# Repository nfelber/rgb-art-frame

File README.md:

# RGB Art Frame

DIY art stand for small engraved artworks based on a custom pcb with several RGB effects.

## The PCB

This design is based on a custom printed circuit board made with KiCad for which all the project files are found in this repository.
The file `design-files/prism-fx_v1_1_gerber.zip` can be uploaded directly to most manufacturers' websites to order your own. You will find the list of all required components for hand soldering in `./design-files/pcb-components-list.csv`.

## The base

The base is laser cut using wood and acrylic (with the intermediate part alternatively 3D printed in translucent material) and held together with four 16mm M2.5 screws.
I also designed a simple cap for the knob which you can 3D print.
Everything was designed using FreeCAD in the project file `model.FCStd`.
You will also find `.stl` and `.dxf` files in the `design-files/` to use straightaway.

Note that some metrics may need to be slightly adjusted depending on the laser cutter or 3D printer.

## The arts

Pretty much anything can be used with the RGB base, but I personnally decided to engrave AI-generated images on wood with an etched layer of acryllic on top to capture light and highlight the edges of the pictures.
I'm not sharing the arts here, as the point to me is that they are unique and personnal.
Be creative!

## The program

The ATtiny85 microcontroller can be easily programmed using an Arduino board as a programmer and with the help of the Arduino IDE.
Many tutorials are available online.
Please note that the USB-C port is only used for powering the circuit board, thus it is **not** possible to program the microcontroller throught it.
Use the PCB's 6 header pins instead.
In order to work with the default `ArduinoISP` sketch, connect them to the Arduino GPIOs as shown below:

```console
      The 6 pins
 .   .   .   .   .   .
[ ] [ ] [ ] [ ] [ ] [ ]
 |   |   |   |   |   |  
 |   |   |   |   |   |    

 +   -   10  13  12  11  <- Arduino GPIOs
```

You will find an example sketch in `prism_fx/prism_fx.ino`.
The sketch shows a way of using interrupts to react to knobs events, the `Adafruit_NeoPixel` library to control the RGB Neopixels, and to storing the last effect state in the permanent EEPROM storage.
Feel free to customize it with you own effects.

In the example sketch, the device cycles through the 3 following modes by pressing down the knob:

1. Effect mode: turing the knob changes the lighting effect among the following:
	- Spectrum: slowly cycle through every color hues.
	- Rainbow: like spectrum, but the LEDs are not synchronized.
	- Static: static color.
	- Fire: fire/candle effect of a static color.
	- Flash: flashes randomly in white.
	- Test: display the current parameter value in binary.
2. Parameter mode: turing the knob changes the value of a parameter between 0 and 31, which has the following result depending on the effect:
	- Spectrum: change cycle speed.
	- Rainbow: change randbow spread in the hue space.
	- Static: change the color.
	- Fire: change the color.
	- Flash: change the frequency of the flashes.
	- Test: display the current parameter value in binary.
3. Brightness mode: turning the knob changes the brightness of the LEDs.

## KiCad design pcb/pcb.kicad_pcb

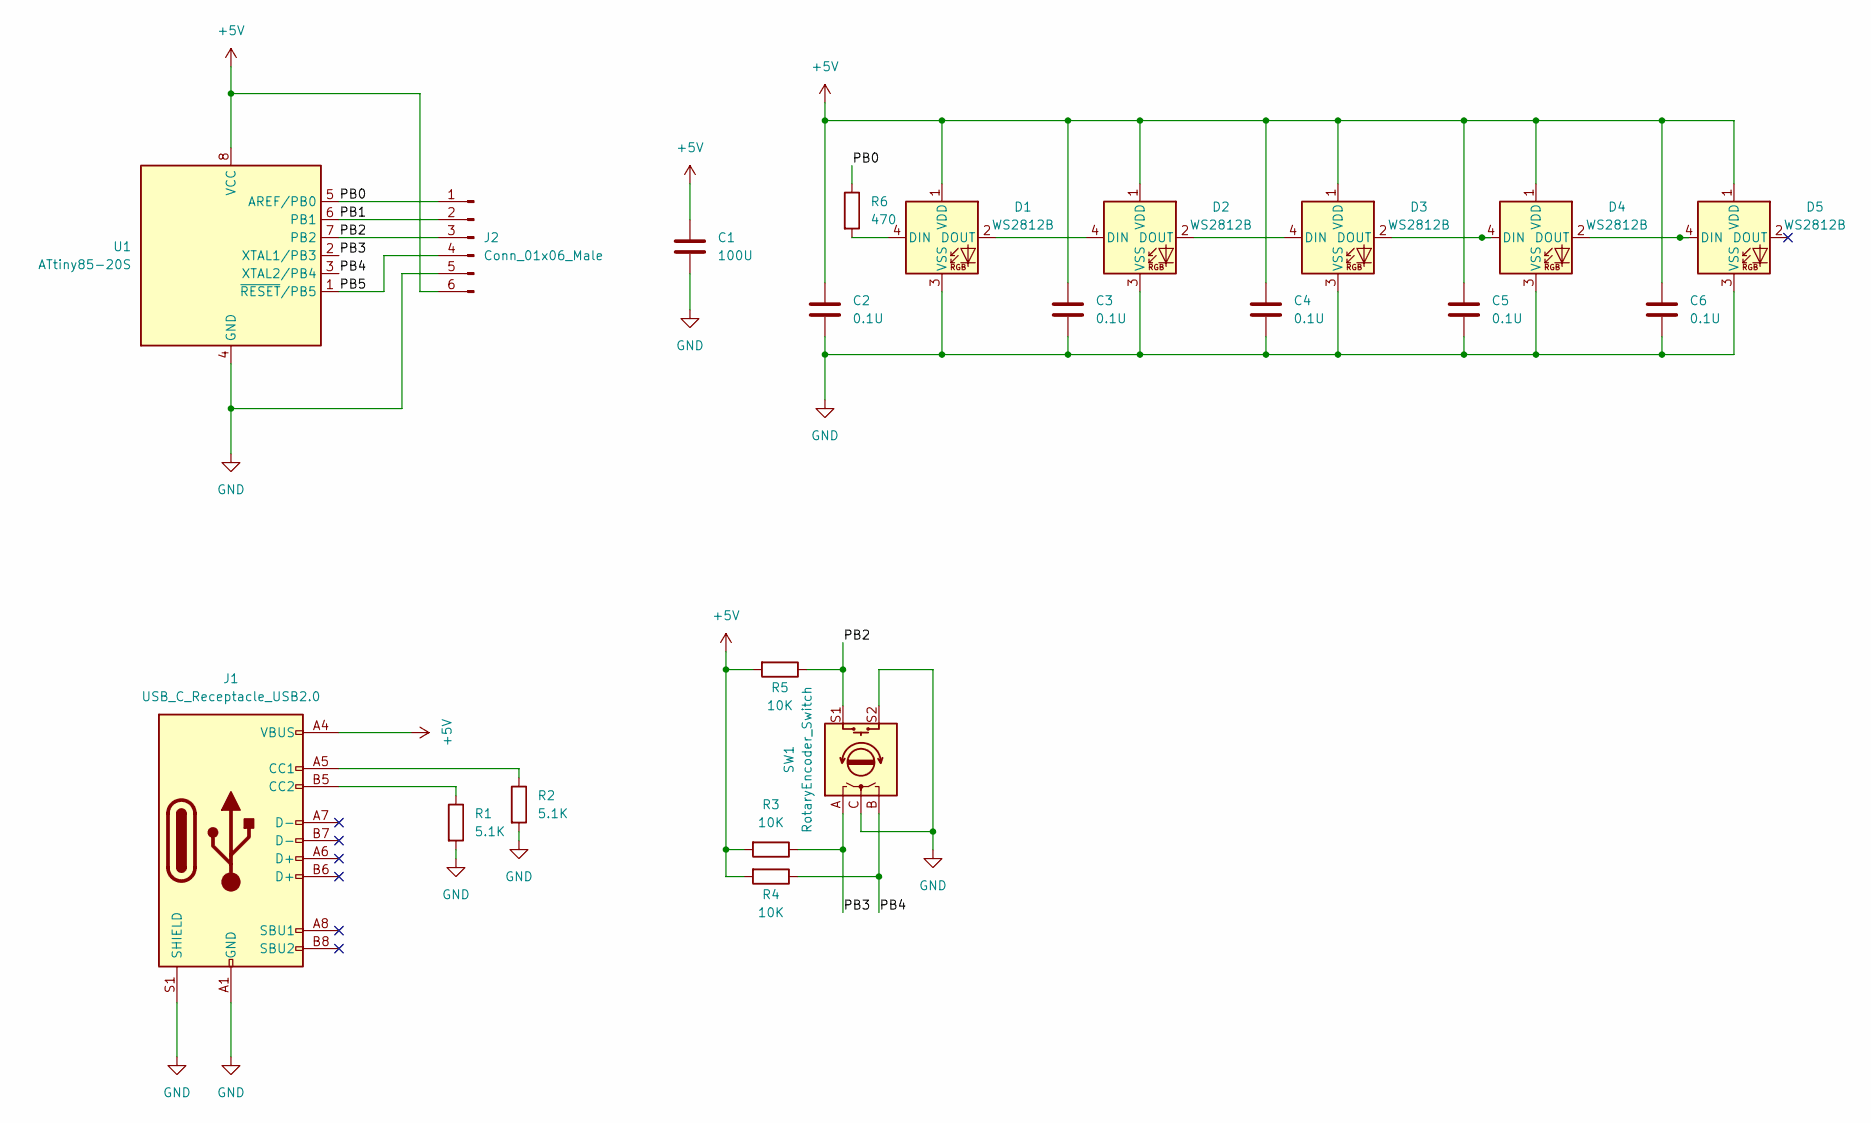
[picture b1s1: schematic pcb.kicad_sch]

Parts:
C1: 100U; C_1210_3225Metric_Pad1.33x2.70mm_HandSolder
C2, C3, C4, C5, C6: 0.1U; C_0603_1608Metric_Pad1.08x0.95mm_HandSolder
D1, D2, D3, D4, D5: WS2812B; LED_WS2812B_PLCC4_5.0x5.0mm_P3.2mm
J1: USB_C_Receptacle_USB2.0; USB_C_Receptacle_HRO_TYPE-C-31-M-12
J2: Conn_01x06_Male; PinHeader_1x06_P2.54mm_Horizontal
R1, R2: 5.1K; R_0603_1608Metric_Pad0.98x0.95mm_HandSolder
R3, R4, R5: 10K; R_0603_1608Metric_Pad0.98x0.95mm_HandSolder
R6: 470; R_0603_1608Metric_Pad0.98x0.95mm_HandSolder
SW1: RotaryEncoder_Switch; EC12D
U1: ATtiny85-20S; SOIC-8W_5.3x5.3mm_P1.27mm

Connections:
+5V: C1.1, C2.1, C3.1, C4.1, C5.1, C6.1, D1.1 (VDD), D2.1 (VDD), D3.1 (VDD), D4.1 (VDD), D5.1 (VDD), J1.A4 (VBUS), J1.A9 (VBUS), J1.B4 (VBUS), J1.B9 (VBUS), J2.6, R3.2, R4.2, R5.2, U1.8 (VCC)
/PB0: J2.1, R6.1, U1.5 (AREF/PB0)
/PB1: J2.2, U1.6 (PB1)
/PB2: J2.3, R5.1, SW1.S1, U1.7 (PB2)
/PB3: R3.1, SW1.A, U1.2 (XTAL1/PB3)
/PB4: R4.1, SW1.B, U1.3 (XTAL2/PB4)
/PB5: J2.4, U1.1 (~RESET/PB5)
GND: C1.2, C2.2, C3.2, C4.2, C5.2, C6.2, D1.3 (VSS), D2.3 (VSS), D3.3 (VSS), D4.3 (VSS), D5.3 (VSS), J1.A1 (GND), J1.A12 (GND), J1.B1 (GND), J1.B12 (GND), J1.S1 (SHIELD), J2.5, R1.2, R2.2, SW1.C, SW1.S2, U1.4 (GND)
unnamed: D1.2 (DOUT), D2.4 (DIN)
unnamed: D1.4 (DIN), R6.2
unnamed: D2.2 (DOUT), D3.4 (DIN)
unnamed: D3.2 (DOUT), D4.4 (DIN)
unnamed: D4.2 (DOUT), D5.4 (DIN)
unnamed: J1.A5 (CC1), R2.1
unnamed: J1.B5 (CC2), R1.1

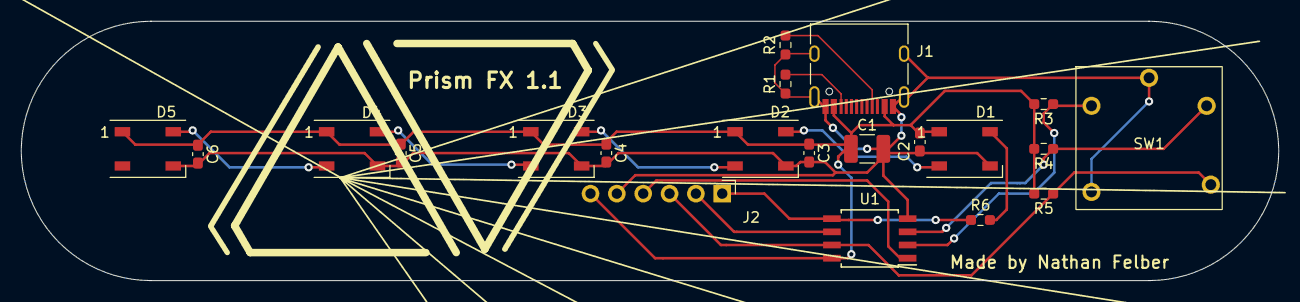
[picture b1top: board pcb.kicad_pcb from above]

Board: 2 copper layers, 121.2 x 25.0 mm, 21 parts (0 on the bottom side), 15 nets.

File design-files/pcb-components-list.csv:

"Source:","/mnt/data/personal-projects/rgb-art-frame/pcb/pcb.kicad_sch"
"Date:","Mon 19 Dec 2022 08:42:54 AM CET"
"Tool:","Eeschema (6.0.9)"
"Generator:","/usr/share/kicad/plugins/bom_csv_grouped_by_value.py"
"Component Count:","21"

"Individual Components:"

"Item","Qty","Reference(s)","Value","LibPart","Footprint","Datasheet"
"","","C1","100U","Device:C","Capacitor_SMD:C_1210_3225Metric_Pad1.33x2.70mm_HandSolder","~"
"","","C2","0.1U","Device:C","Capacitor_SMD:C_0603_1608Metric_Pad1.08x0.95mm_HandSolder","~"
"","","C3","0.1U","Device:C","Capacitor_SMD:C_0603_1608Metric_Pad1.08x0.95mm_HandSolder","~"
"","","C4","0.1U","Device:C","Capacitor_SMD:C_0603_1608Metric_Pad1.08x0.95mm_HandSolder","~"
"","","C5","0.1U","Device:C","Capacitor_SMD:C_0603_1608Metric_Pad1.08x0.95mm_HandSolder","~"
"","","C6","0.1U","Device:C","Capacitor_SMD:C_0603_1608Metric_Pad1.08x0.95mm_HandSolder","~"
"","","D1","WS2812B","LED:WS2812B","LED_SMD:LED_WS2812B_PLCC4_5.0x5.0mm_P3.2mm","https://cdn-shop.adafruit.com/datasheets/WS2812B.pdf"
"","","D2","WS2812B","LED:WS2812B","LED_SMD:LED_WS2812B_PLCC4_5.0x5.0mm_P3.2mm","https://cdn-shop.adafruit.com/datasheets/WS2812B.pdf"
"","","D3","WS2812B","LED:WS2812B","LED_SMD:LED_WS2812B_PLCC4_5.0x5.0mm_P3.2mm","https://cdn-shop.adafruit.com/datasheets/WS2812B.pdf"
"","","D4","WS2812B","LED:WS2812B","LED_SMD:LED_WS2812B_PLCC4_5.0x5.0mm_P3.2mm","https://cdn-shop.adafruit.com/datasheets/WS2812B.pdf"
"","","D5","WS2812B","LED:WS2812B","LED_SMD:LED_WS2812B_PLCC4_5.0x5.0mm_P3.2mm","https://cdn-shop.adafruit.com/datasheets/WS2812B.pdf"
"","","J1","USB_C_Receptacle_USB2.0","Connector:USB_C_Receptacle_USB2.0","Connector_USB:USB_C_Receptacle_HRO_TYPE-C-31-M-12","https://www.usb.org/sites/default/files/documents/usb_type-c.zip"
"","","J2","Conn_01x06_Male","Connector:Conn_01x06_Male","Connector_PinHeader_2.54mm:PinHeader_1x06_P2.54mm_Horizontal","~"
"","","R1","5.1K","Device:R","Resistor_SMD:R_0603_1608Metric_Pad0.98x0.95mm_HandSolder","~"
"","","R2","5.1K","Device:R","Resistor_SMD:R_0603_1608Metric_Pad0.98x0.95mm_HandSolder","~"
"","","R3","10K","Device:R","Resistor_SMD:R_0603_1608Metric_Pad0.98x0.95mm_HandSolder","~"
"","","R4","10K","Device:R","Resistor_SMD:R_0603_1608Metric_Pad0.98x0.95mm_HandSolder","~"
"","","R5","10K","Device:R","Resistor_SMD:R_0603_1608Metric_Pad0.98x0.95mm_HandSolder","~"
"","","R6","470","Device:R","Resistor_SMD:R_0603_1608Metric_Pad0.98x0.95mm_HandSolder","~"
"","","SW1","RotaryEncoder_Switch","Device:RotaryEncoder_Switch","pcb:EC12D","~"
"","","U1","ATtiny85-20S","MCU_Microchip_ATtiny:ATtiny85-20S","Package_SO:SOIC-8W_5.3x5.3mm_P1.27mm","http://ww1.microchip.com/downloads/en/DeviceDoc/atmel-2586-a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"



"Collated Components:"

"Item","Qty","Reference(s)","Value","LibPart","Footprint","Datasheet"
"1","1","C1","100U","Device:C","Capacitor_SMD:C_1210_3225Metric_Pad1.33x2.70mm_HandSolder","~"
"2","5","C2, C3, C4, C5, C6","0.1U","Device:C","Capacitor_SMD:C_0603_1608Metric_Pad1.08x0.95mm_HandSolder","~"
"3","5","D1, D2, D3, D4, D5","WS2812B","LED:WS2812B","LED_SMD:LED_WS2812B_PLCC4_5.0x5.0mm_P3.2mm","https://cdn-shop.adafruit.com/datasheets/WS2812B.pdf"
"4","1","J1","USB_C_Receptacle_USB2.0","Connector:USB_C_Receptacle_USB2.0","Connector_USB:USB_C_Receptacle_HRO_TYPE-C-31-M-12","https://www.usb.org/sites/default/files/documents/usb_type-c.zip"
"5","1","J2","Conn_01x06_Male","Connector:Conn_01x06_Male","Connector_PinHeader_2.54mm:PinHeader_1x06_P2.54mm_Horizontal","~"
"6","2","R1, R2","5.1K","Device:R","Resistor_SMD:R_0603_1608Metric_Pad0.98x0.95mm_HandSolder","~"
"7","3","R3, R4, R5","10K","Device:R","Resistor_SMD:R_0603_1608Metric_Pad0.98x0.95mm_HandSolder","~"
"8","1","R6","470","Device:R","Resistor_SMD:R_0603_1608Metric_Pad0.98x0.95mm_HandSolder","~"
"9","1","SW1","RotaryEncoder_Switch","Device:RotaryEncoder_Switch","pcb:EC12D","~"
"10","1","U1","ATtiny85-20S","MCU_Microchip_ATtiny:ATtiny85-20S","Package_SO:SOIC-8W_5.3x5.3mm_P1.27mm","http://ww1.microchip.com/downloads/en/DeviceDoc/atmel-2586-a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"
